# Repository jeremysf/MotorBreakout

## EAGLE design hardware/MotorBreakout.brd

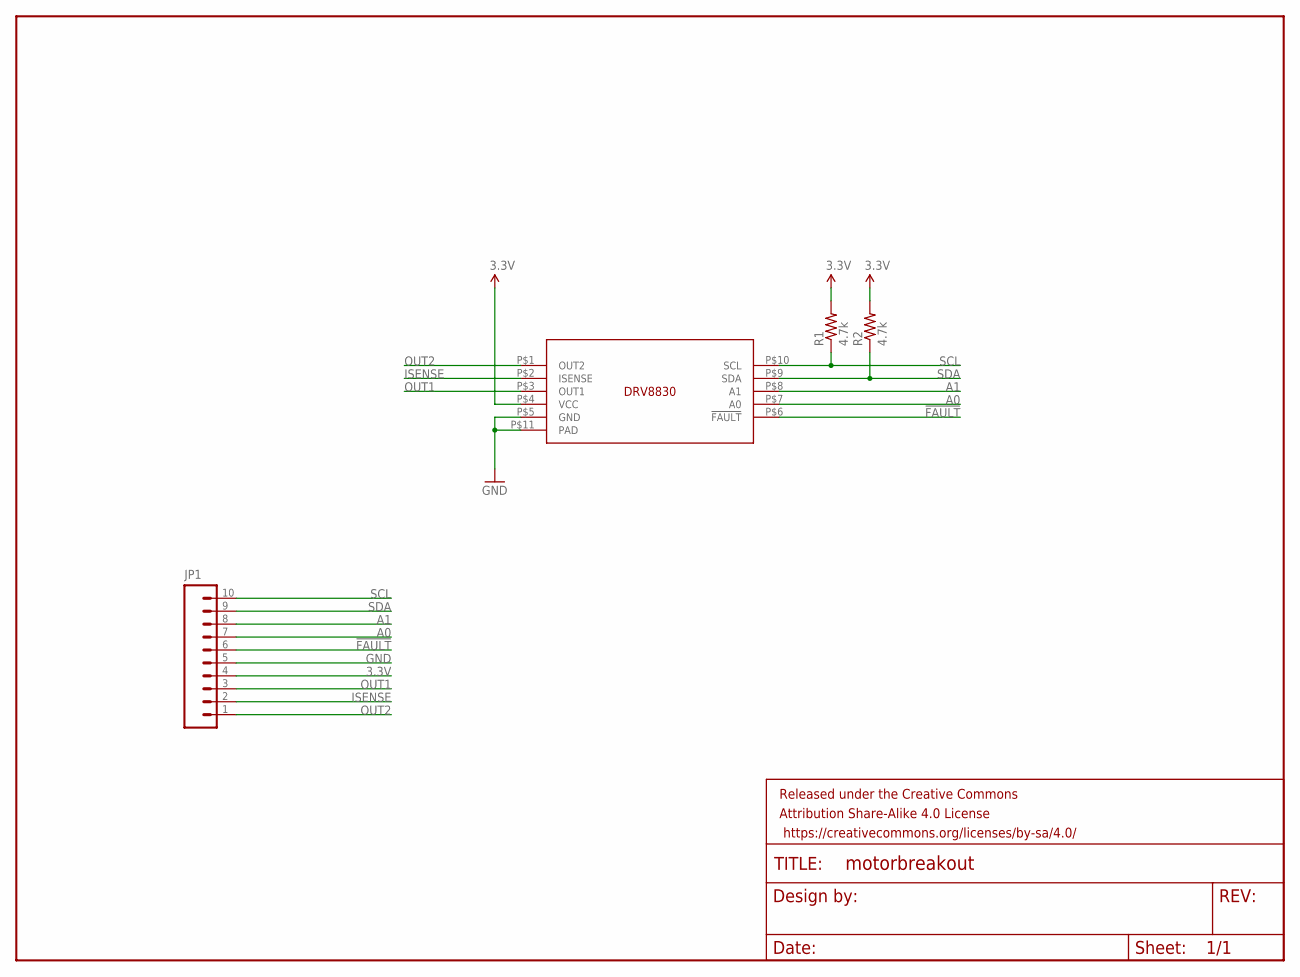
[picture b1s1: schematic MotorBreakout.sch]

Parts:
FRAME1: FRAME-LETTERNO_PACKAGE; DUMMY
JP1: M10LOCK_LONGPADS; 1X10_LOCK_LONGPADS
R1, R2: 4.7k; 0402-RES
U$1: DRV8830

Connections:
3.3V: JP1.4, R1.2, R2.2, U$1.P$4 (VCC)
!FAULT: JP1.6, U$1.P$6 (!FAULT)
A0: JP1.7, U$1.P$7 (A0)
A1: JP1.8, U$1.P$8 (A1)
GND: JP1.5, U$1.P$5 (GND), U$1.P$11 (PAD)
ISENSE: JP1.2, U$1.P$2 (ISENSE)
OUT1: JP1.3, U$1.P$3 (OUT1)
OUT2: JP1.1, U$1.P$1 (OUT2)
SCL: JP1.10, R1.1, U$1.P$10 (SCL)
SDA: JP1.9, R2.1, U$1.P$9 (SDA)

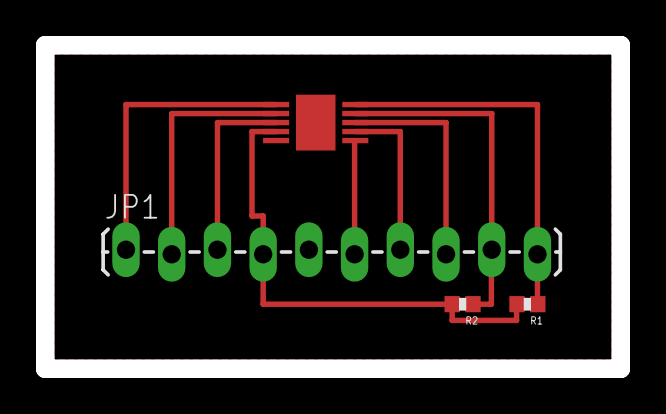
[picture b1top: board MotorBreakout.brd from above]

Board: 2 copper layers, 32.0 x 18.0 mm, 5 parts (0 on the bottom side), 10 nets.

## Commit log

2015-09-29 Initial commit.
2015-09-29 Basic breakout complete.y

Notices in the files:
parts and their libraries:
SparkFun-Aesthetics: Licensing: Creative Commons ShareAlike 4.0 International - https://creativecommons.org/licenses/by-sa/4.0
SparkFun-Aesthetics: Released under the Creative Commons Attribution Share-Alike 4.0 License
SparkFun-Aesthetics: https://creativecommons.org/licenses/by-sa/4.0
